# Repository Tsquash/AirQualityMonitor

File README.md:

# Air Quality Monitor

AQM is an ESP32-C6-based, Matter compatible, indoor air-quality monitor. It measures carbon
dioxide, temperature, humidity, VOC, and NOx, displays the latest readings on an e-paper
display, and publishes its measurements through Matter over Wi-Fi. It can also pair with
the companion PM sensor [particle](https://github.com/Tsquash/particle/) over Bluetooth
Low Energy (BLE) to add PM2.5 and PM10 measurements to its existing Matter endpoint.

## Hardware

- **MCU:** Seeed Studio XIAO ESP32-C6
- **Carbon-dioxide sensor:** Sensirion SCD41
- **Temperature and humidity sensor:** ASAIR DHT20
  - Before assembly, pry open the DHT20 module's plastic case and desolder its
    two 10 kΩ I2C pull-up resistors. The AQM PCB already supplies the I2C
    pull-ups, so leaving the module's resistors may cause unexpected errors
- **VOC and NOx sensor:** Sensirion SGP41
  - uses the Sensirion Gas Index Algorithm
- **RTC:** Analog Devices MAX31328
- **Display:** 3.7-inch, 416 x 240 pixel monochrome e-paper display
  - GDEY037T03 panel/UC8253 driver, driven with GxEPD2 and Adafruit GFX libaries
- **PM interconnect:** BLE link to the companion Matter PM sensor
- **Enclosure:** acrylic sandwich-style enclosure

The primary pin assignments are defined in
[`main/sense.cpp`](main/sense.cpp), [`main/screen.cpp`](main/screen.cpp), and
[`main/buttons.h`](main/buttons.h):

| Signal | GPIO |
| --- | ---: |
| I2C SDA | 22 |
| I2C SCL | 23 |
| RTC interrupt | 2 |
| E-paper MOSI | 18 |
| E-paper SCK | 19 |
| E-paper chip select | 17 |
| E-paper data/command | 21 |
| E-paper reset | 20 |
| Top button | 0 |
| Bottom button | 1 |

## Operating modes

### Matter commissioning

The AQM is a Matter-over-Wi-Fi device and requires a 2.4 GHz Wi-Fi network and a
Matter controller. On an uncommissioned device, the display shows the Matter
QR code and manual pairing code. Scan the QR code with a Matter-compatible
controller app and complete the app's setup flow for Matter devices. This project
uses Matter development credentials and is not Matter-certified, so the controller
may ask for confirmation before adding it. Although all devices have the same pairing
code, multiple AQM devices on one network is tested working.

After commissioning, the AQM obtains local time over the network. It determines
the UTC offset from `https://ipapi.co/utc_offset/`, synchronizes system time with
`pool.ntp.org`, writes that time to the MAX31328 RTC, and attempts another RTC
sync once per hour. The hourly sync re-queries the current UTC offset, and supports DST.
If the RTC already contains valid time, the local display can continue operating
before Matter commissioning completes.

### Normal operation

The SGP41 is sampled once per second to maintain the VOC and NOx gas-index
algorithms. Ten seconds before each minute, the RTC wakes the firmware to take
new DHT20 and SCD41 readings, finalize any PM reading received for that minute,
update the Matter attributes, and append CO2, VOC, and NOx values to the
60-sample history. At the start of the next minute, the active display page is
redrawn.

The main page shows the date, time, temperature, relative humidity, CO2, VOC,
NOx, and the overall air-quality level. The second page graphs the most recent
60 one-minute CO2, VOC, and NOx readings. The display performs a full refresh at
`:00` and `:30` each hour and uses partial refreshes between them.

### Linked to a PM sensor

The AQM can pair with the companion Matter PM sensor over BLE.

#### Pairing protocol

Put both devices into pairing mode and keep them nearby:

1. Hold the AQM's bottom button while booting it. Release the button when the
   AQM displays `Pairing with PM`.
2. Start or restart the PM sensor in pairing mode. A new PM sensor automatically
   enters pairing mode on its first boot. On later boots, hold its pair
   button or factory reset button  to force another pairing attempt.
3. Leave both devices powered and nearby until each displays `Pairing
   Successful`. Both pairing windows last up to 120 seconds.

The devices discover and authenticate each other automatically. If either device displays `Pairing
Timed Out`, put both devices back into pairing mode and retry with them nearby.
On success, the PM peer is saved in non-volatile storage and the AQM reconnects
to it automatically on later boots.

The AQM sends its RTC time and measurement schedule to the PM sensor. The PM
sensor returns one-minute PM1.0, PM2.5, and PM10 averages, which the AQM exposes
through Matter. If the BLE connection is interrupted, the AQM retains the last
PM reading for up to three missed minutes and clears it after the fourth. All
other AQM sensing and display functions continue without a linked PM sensor.

## Buttons

| Button | GPIO | At boot | During operation |
| --- | ---: | --- | --- |
| Top | 0 | Erase the complete NVS partition, including Matter commissioning, Wi-Fi credentials, and the saved PM peer | No action |
| Bottom | 1 | Enter PM-pairing mode and replace the previously saved PM peer after successful pairing | Change display page |

A boot action requires the button to be held continuously for at least one second
during the two-second startup check. Factory reset takes priority if both buttons are held.
After a factory reset, the device restarts and displays its Matter commissioning screen.

## Readings

The AQM measures or receives the following values:

- ☁️ **CO2:** measured by the SCD41 and reported in ppm
  - +/- (50 ppm + 2.5% of the reading) from 400 to 1,000 ppm
  - +/- (50 ppm + 3% of the reading) from 1,001 to 2,000 ppm
  - +/- (40 ppm + 5% of the reading) from 2,001 to 5,000 ppm
- 🌡️ **Temperature and 💧relative humidity:** measured by the DHT20
  - Temperature accuracy: +/- 0.75 degrees C
  - Relative-humidity accuracy: +/- 4% RH
- 🍃 **VOC and 💨 NOx indices:** measured by the SGP41 and calculated with the
  [Sensirion Gas Index Algorithm](https://sensirion.com/products/downloads?category=Gas+analyzers)
  as unitless index points from 1 to 500; they are relative air-quality signals,
  not measured gas concentrations
  - VOC's long-term average is 100, lower values indicate improving conditions
    and higher values indicate worsening conditions
  - NOx's typical baseline is 1, values above 1 indicate NOx events
  - Allow approximately one hour for reliable VOC detection and six hours for
    reliable NOx event detection after startup
  - Matter has concentration-measurement clusters for these readings but no
    unit for index points. For compatibility, the firmware
    currently publishes each index through its corresponding concentration
    cluster with the unit set to `µg/m³`. That displayed unit is incorrect:
    the numeric values are still unitless VOC and NOx indices and must not be
    interpreted as physical concentrations.
- **PM1.0, PM2.5, and PM10:** received in micrograms per cubic meter from a
  linked Matter PM sensor

The overall air-quality value is the worst of the current CO2, VOC, NOx, PM1.0,
PM2.5, and PM10 bands. It is reported as Good, Fair, Moderate, Poor, Very Poor,
or Extremely Poor.

## Build, upload, and serial output

Install [PlatformIO](https://platformio.org/) and the Espressif platform
dependencies, connect the XIAO ESP32-C6, then run these commands from the
project directory:

```sh
pio run -e esp32c6
pio run -e esp32c6 -t upload
pio device monitor -b 115200
```

The PlatformIO environment is defined in [`platformio.ini`](platformio.ini).
The project uses the Arduino and ESP-IDF frameworks and is configured for the
`seeed_xiao_esp32c6` board. Serial diagnostics run at 115200 baud. Upload-port
selection may need to be configured for the host computer. A clean or first
compile can take 10 minutes or longer while PlatformIO builds the ESP-IDF and
Matter dependencies, but later incremental builds are faster since the build is cached.

### Bundled MAX31328 library

[`lib/Max31328RTC`](lib/Max31328RTC) is a local fork of Analog Devices'
[MAX31328 Arduino Driver](https://github.com/analogdevicesinc/MAX31328-Arduino-Driver).
The upstream library did not work unchanged with the ESP32-C6, so this fork:

- leaves I2C initialization to the firmware instead of calling `Wire.begin()`
  from the RTC constructor, which would initialize the bus before the AQM
  assigns its SDA and SCL pins;
- casts the write buffer to the byte-pointer type required by the ESP32-C6
  Arduino `Wire.write()` overload, fixing the compile error; and
- updates the time, calendar, and control/status output structures only after a
  successful I2C read, preventing failed reads from copying invalid data.

The upstream driver is licensed under Apache-2.0, which permits modification
and redistribution. The fork retains the upstream copyright and modification
notices and includes the complete license at
[`lib/Max31328RTC/LICENSE.txt`](lib/Max31328RTC/LICENSE.txt).

## License

The original firmware, PCB and schematic files, manufacturing files, enclosure
files, UI assets, and documentation in this repository are available under the
[Apache License 2.0](LICENSE). You may use,
modify, manufacture from, and share, the original or modified project, provided that you follow the license terms :)

## Project layout

```text
main/                  Firmware source, embedded display assets, and component config
  myBitmap/            Embedded monochrome display bitmaps
  myFont/              Embedded Adafruit GFX fonts
lib/                   Project-local libraries, including the altered MAX31328 driver
KICAD/                 PCB schematic, layout, symbols, and footprints
Production/            Manufacturing BOMs and Gerber archive
2D/                    Enclosure and PCB cutout drawings
3D/                    Board, spacer, and enclosure models
UI/                    Display mockups, fonts, and bitmaps
.vscode/               VS Code project configuration
platformio.ini         PlatformIO build environment
LICENSE                Apache License 2.0 project license
sdkconfig.defaults.*   ESP-IDF default configurations
huge_app.csv           ESP-IDF flash partition table
```

The primary firmware files are:

- [`main/main.cpp`](main/main.cpp): boot flow, Matter startup, scheduling, and
  the main loop
- [`main/sense.cpp`](main/sense.cpp): sensor initialization and sampling, gas
  indices, RTC alarms, network time, and overall air-quality calculation
- [`main/screen.cpp`](main/screen.cpp): e-paper initialization, status screens,
  measurement pages, and history graphs
- [`main/buttons.cpp`](main/buttons.cpp): boot-hold detection and display-page
  button handling
- [`main/matter_air_quality_sensor.cpp`](main/matter_air_quality_sensor.cpp):
  Matter endpoint, measurement clusters, and attribute updates
- [`main/pm_link.cpp`](main/pm_link.cpp): BLE PM pairing, reconnection, timing,
  and PM-reading reception
- [`main/pm_protocol.h`](main/pm_protocol.h): BLE data structures shared with
  the companion PM project

## Troubleshooting

- **Matter commissioning does not complete:** Confirm that the Matter controller
  and 2.4 GHz Wi-Fi network are online and that the phone is close enough for
  BLE commissioning. Factory-reset the AQM before retrying it on a different
  Matter fabric or Wi-Fi network.
- **Time or date is incorrect:** The AQM needs network access to the timezone
  API and NTP server. Check the Wi-Fi network's Internet connectivity and
  inspect the serial log for `[Time]` or `[RTC]` errors.
- **A sensor reports invalid or fixed readings:** Check the shared I2C wiring,
  sensor power, and serial output. The firmware logs DHT20, SCD41, SGP41, and RTC
  communication errors.
- **VOC or NOx readings seem unstable after startup:** Leave the device powered
  while the gas-index algorithms learn their baseline. VOC needs about one hour
  and NOx about six hours for reliable event detection.
- **For most other errors:** Check the serial log! I tried to leave debugging print statements that were helpful to me during development.

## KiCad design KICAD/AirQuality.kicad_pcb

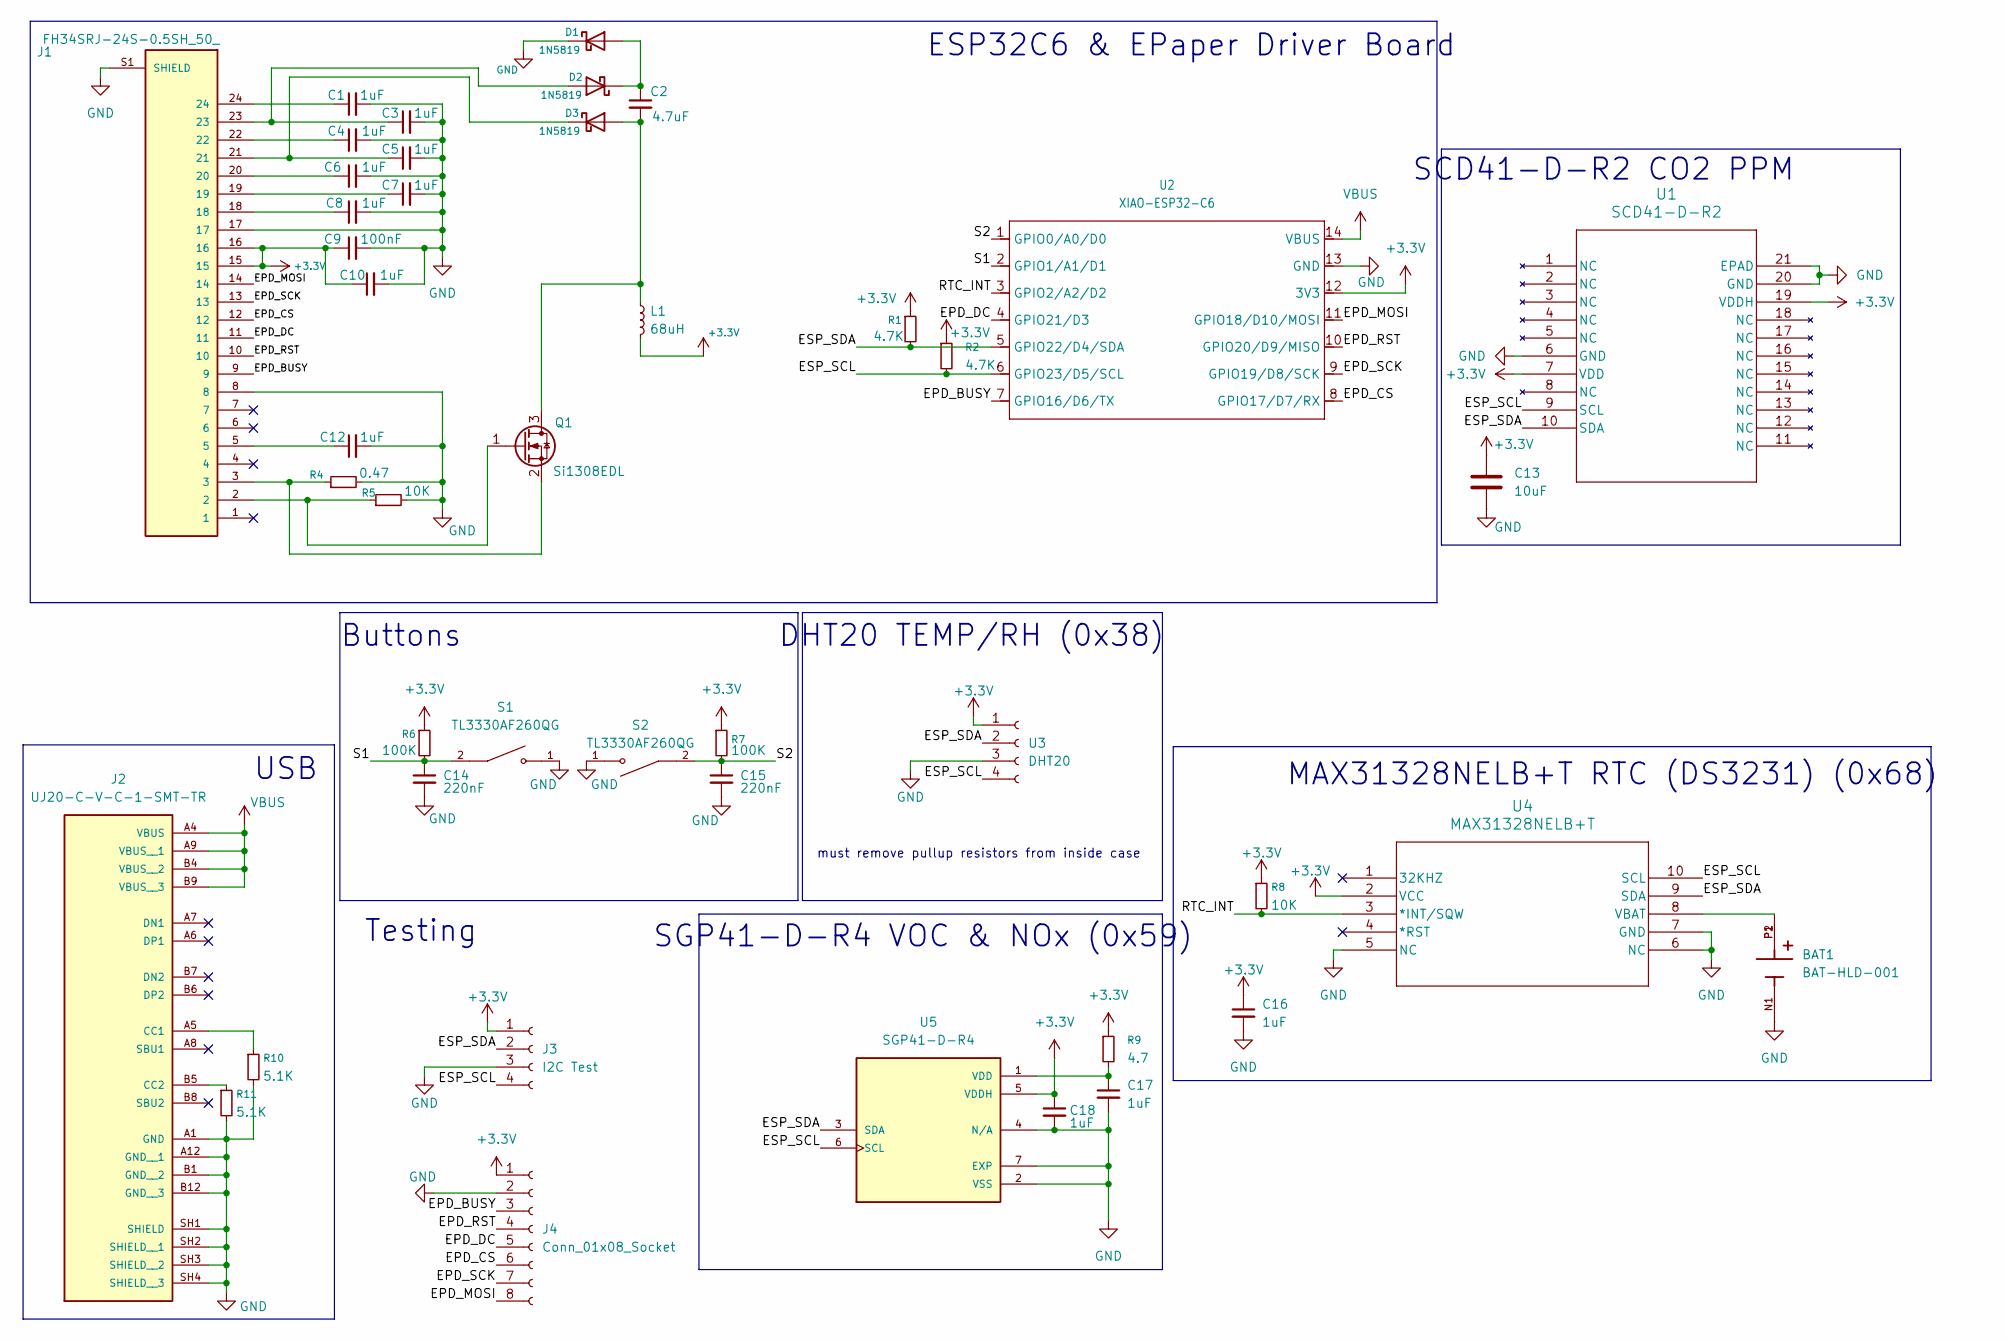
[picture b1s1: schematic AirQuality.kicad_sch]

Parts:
BAT1: BAT-HLD-001; BAT_BAT-HLD-001; PARTREV C
C1, C3, C4, C5, C6, C7, C8, C10, C12, C16, C17, C18: 1uF; C_0603_1608Metric
C2: 4.7uF; C_0603_1608Metric
C9: 100nF; C_0603_1608Metric
C13: 10uF; C_0603_1608Metric
C14, C15: 220nF; C_0603_1608Metric
D1, D2, D3: 1N5819; D_SOD-123
J1: FH34SRJ-24S-0.5SH_50_; HRS_FH34SRJ-24S-0.5SH_50_
J2: UJ20-C-V-C-1-SMT-TR; CUI_UJ20-C-V-C-1-SMT-TR; PARTREV 1.0
J3: I2C Test; PinHeader_1x04_P2.54mm_Vertical
J4: Conn_01x08_Socket; PinHeader_1x08_P2.54mm_Vertical
L1: 68uH; L_0805_2012Metric
Q1: Si1308EDL; SOT-323_SC-70
R1, R2: 4.7K; R_0603_1608Metric
R4: 0.47; R_0603_1608Metric
R5, R8: 10K; R_0603_1608Metric
R6, R7: 100K; R_0603_1608Metric
R9: 4.7; R_0603_1608Metric
R10, R11: 5.1K; R_0603_1608Metric
S1, S2: TL3330AF260QG; SW_TL3330AF260QG; PARTREV B
U1: SCD41-D-R2; QFN20_SCD41-D-R2_SEN
U2: XIAO-ESP32-C6; XIAO-ESP32C6-DIP
U3: DHT20; PinHeader_1x04_P2.54mm_Vertical
U4: MAX31328NELB+T; 21-0140AK_L1055M-1_MXM
U5: SGP41-D-R4; XDCR_SGP41-D-R4; PARTREV 1.0

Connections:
+3.3V: C9.1, C10.1, C13.1, C16.1, C18.1, J1.15, J1.16, J3.1, J4.1, L1.2, R1.1, R2.1, R6.1, R7.1, R8.1, R9.1, U1.7 (VDD), U1.19 (VDDH), U2.12 (3V3), U3.1, U4.2 (VCC), U5.5 (VDDH); also elsewhere on the board
/EPD_BUSY: J1.9, J4.3, U2.7 (GPIO16/D6/TX)
/EPD_CS: J1.12, J4.6, U2.8 (GPIO17/D7/RX)
/EPD_DC: J1.11, J4.5, U2.4 (GPIO21/D3)
/EPD_MOSI: J1.14, J4.8, U2.11 (GPIO18/D10/MOSI)
/EPD_RST: J1.10, J4.4, U2.10 (GPIO20/D9/MISO)
/EPD_SCK: J1.13, J4.7, U2.9 (GPIO19/D8/SCK)
/ESP_SCL: J3.4, R2.2, U1.9 (SCL), U2.6 (GPIO23/D5/SCL), U3.4, U4.10 (SCL), U5.6 (SCL)
/ESP_SDA: J3.2, R1.2, U1.10 (SDA), U2.5 (GPIO22/D4/SDA), U3.2, U4.9 (SDA), U5.3 (SDA)
/RTC_INT: R8.2, U2.3 (GPIO2/A2/D2), U4.3 (*INT/SQW)
/S1: C14.1, R6.2, S1.2, U2.2 (GPIO1/A1/D1)
/S2: C15.1, R7.2, S2.2, U2.1 (GPIO0/A0/D0)
GND: BAT1.N1, C1.2, C3.2, C4.2, C5.2, C6.2, C7.2, C8.2, C9.2, C10.2, C12.2, C13.2, C14.2, C15.2, C16.2, C17.2, C18.2, D1.1 (K), J1.8, J1.17, J1.S1 (SHIELD), J1.S2 (SHIELD), J2.A1 (GND), J2.A12 (GND__1), J2.B1 (GND__2), J2.B12 (GND__3), J2.SH1 (SHIELD), J2.SH2 (SHIELD__1), J2.SH3 (SHIELD__2), J2.SH4 (SHIELD__3), J3.3, J4.2, R4.2, R5.2, R10.2, R11.2, S1.1, S2.1, U1.6 (GND), U1.20 (GND), U1.21 (EPAD), U2.13 (GND), U3.3, U4.5 (NC), U4.6 (NC), U4.7 (GND), U5.2 (VSS), U5.4 (N/A), U5.7 (EXP); also elsewhere on the board
unnamed: C1.1, J1.24
unnamed: C4.1, J1.22
unnamed: C6.1, J1.20
unnamed: C7.1, J1.19
unnamed: C8.1, J1.18
unnamed: C12.1, J1.5
unnamed: C2.1, D1.2 (A), D2.1 (K)
unnamed: C3.1, D2.2 (A), J1.23
unnamed: C2.2, D3.2 (A), L1.1, Q1.3 (D)
unnamed: C5.1, D3.1 (K), J1.21
unnamed 23: J1.4; also elsewhere on the board
unnamed: J2.A5 (CC1), R10.1
unnamed: J2.B5 (CC2), R11.1
unnamed: J1.2, Q1.1 (G), R5.1
unnamed: J1.3, Q1.2 (S), R4.1
unnamed: BAT1.P1, BAT1.P2, U4.8 (VBAT)
unnamed: C17.1, R9.2, U5.1 (VDD)
VBUS: J2.A4 (VBUS), J2.A9 (VBUS__1), J2.B4 (VBUS__2), J2.B9 (VBUS__3), U2.14 (VBUS)

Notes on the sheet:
SGP41-D-R4 VOC & NOx (0x59)
ESP32C6 & EPaper Driver Board
DHT20 TEMP/RH (0x38)
USB
Buttons
Testing
MAX31328NELB+T RTC (DS3231) (0x68)
SCD41-D-R2 CO2 PPM
must remove pullup resistors from inside case

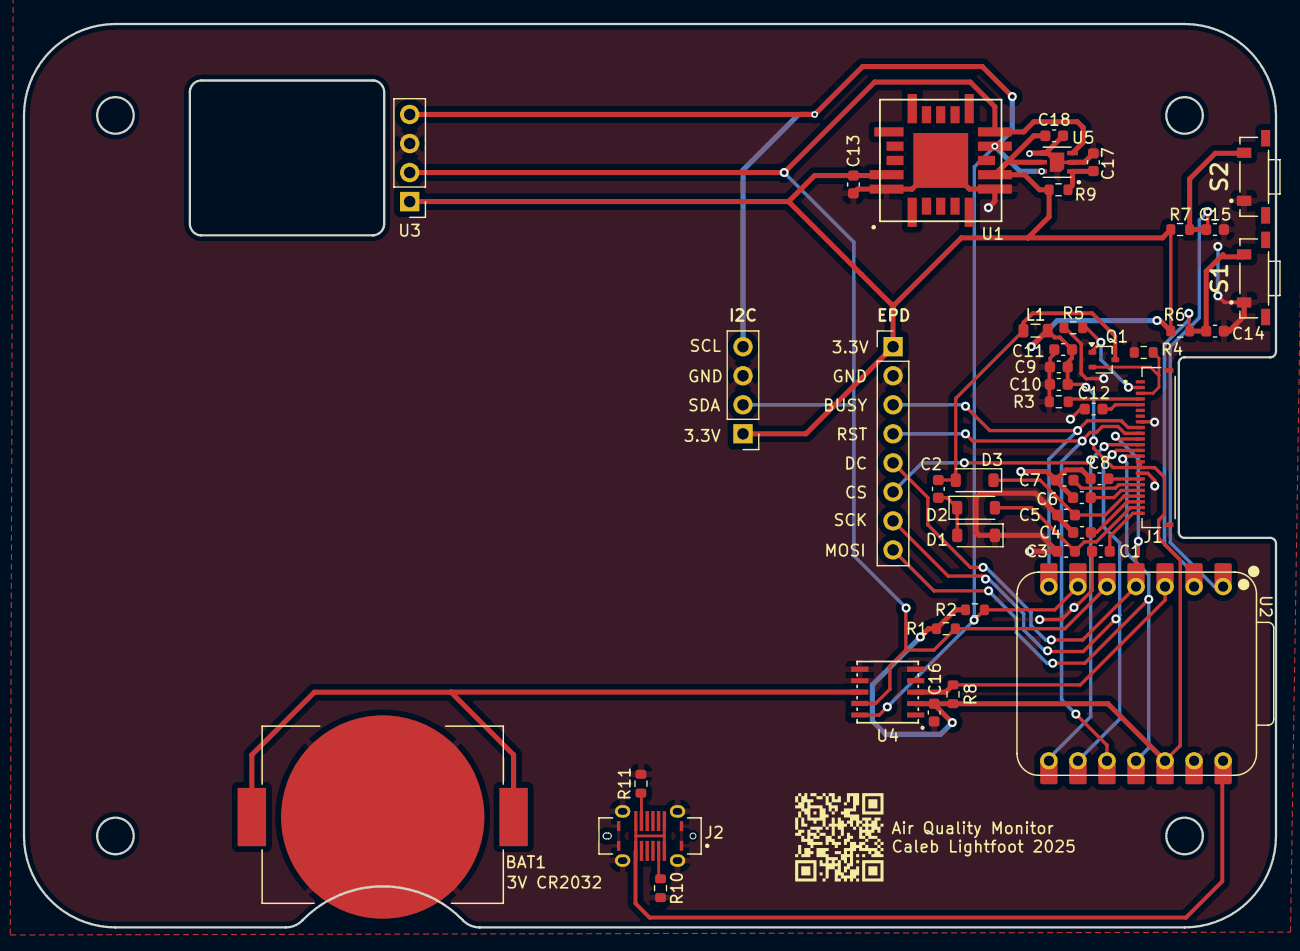
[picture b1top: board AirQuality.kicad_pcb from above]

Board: 4 copper layers, 109.5 x 79.0 mm, 46 parts (0 on the bottom side), 31 nets.

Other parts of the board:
C11: 4.7uF; C_0603_1608Metric
R3: 0; R_0603_1608Metric

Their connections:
+3.3V: C11.1; also elsewhere on the board
GND: C11.2, R3.2; also elsewhere on the board
unnamed 23: R3.1; also elsewhere on the board

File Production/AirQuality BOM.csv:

Reference,Qty,Value,Footprint,,
BAT1,1,BAT-HLD-001,AirQualityFootprints:BAT_BAT-HLD-001,,
"C1,C3,C4,C5,C6,C7,C8,C10,C12,C16,C17,C18",12,1uF,Capacitor_SMD:C_0603_1608Metric,,
"C2,C11",2,4.7uF,Capacitor_SMD:C_0603_1608Metric,,
C9,1,100nF,Capacitor_SMD:C_0603_1608Metric,,
C13,1,10uF,Capacitor_SMD:C_0603_1608Metric,,
"C14,C15",2,220nF,Capacitor_SMD:C_0603_1608Metric,,*need to desolder two
"D1,D2,D3",3,1N5819,Diode_SMD:D_SOD-123,,
J1,1,FH34SRJ-24S-0.5SH_50_,AirQualityFootprints:HRS_FH34SRJ-24S-0.5SH_50_,,
J2,1,UJ20-C-V-C-1-SMT-TR,AirQualityFootprints:CUI_UJ20-C-V-C-1-SMT-TR,,
L1,1,68uH,Inductor_SMD:L_0805_2012Metric,,
Q1,1,Si1308EDL,Package_TO_SOT_SMD:SOT-323_SC-70,,
"R1,R2",2,4.7K,Resistor_SMD:R_0603_1608Metric,,
R3,1,DNP,Resistor_SMD:R_0603_1608Metric,,
R4,1,0.47,Resistor_SMD:R_0603_1608Metric,,
R5,1,10K/0,Resistor_SMD:R_0603_1608Metric,,
"R6,R7",2,100K,Resistor_SMD:R_0603_1608Metric,,
R8,1,10K,Resistor_SMD:R_0603_1608Metric,,
R9,1,4.7,Resistor_SMD:R_0603_1608Metric,,
"R10,R11",2,5.1K,Resistor_SMD:R_0603_1608Metric,,
"S1,S2",2,TL3330AF260QG,AirQualityFootprints:SW_TL3330AF260QG,,
U1,1,SCD41-D-R2,AirQualityFootprints:QFN20_SCD41-D-R2_SEN,,
U2,1,XIAO-ESP32-C6,AirQualityFootprints:XIAO-ESP32C6-DIP,,*need to desolder one
U3,1,DHT20,Connector_PinHeader_2.54mm:PinHeader_1x04_P2.54mm_Vertical,,*need to desolder one
U4,1,MAX31328NELB+T,AirQualityFootprints:21-0140AK_L1055M-1_MXM,,*need to desolder one
U5,1,SGP41-D-R4,AirQualityFootprints:XDCR_SGP41-D-R4,,

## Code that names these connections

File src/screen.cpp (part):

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
#define GxEPD2_DISPLAY_CLASS GxEPD2_BW
#define GxEPD2_DRIVER_CLASS GxEPD2_370_GDEY037T03 // GDEY037T03 240x416, UC8253
#define EPD_DC 21
#define EPD_CS 17
#define EPD_SCK   19
#define EPD_MOSI  18
#define EPD_MISO -1 // not reading from screen
#define EPD_BUSY -1 // can set to -1 to not use a pin (will wait a fixed delay)
#define SRAM_CS -1 // use internal RAM
#define EPD_RESET 20  // can set to -1 and share with microcontroller Reset!
#define EPD_SPI &epd_spi // primary SPI
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
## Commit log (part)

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2025-12-30 initial
2025-12-31 added battery monitoring, shows percent on screen
2025-12-31 working Eink with battery %, temp, and humidity showing (basic)
2025-12-31 added lib dep for interrupt buttons
2025-12-31 removed .vscode folder from project
2025-12-31 removed unused EPD drivers and panels for compile time, added basic (non-working) button functions
2025-12-31 check if buttons held at boot working
2025-12-31 added license, added wifi functionality for setting RTC and captive portal config, changed C6 partition scheme to free up flash, modified boot button logic, and removed EPD examples
2026-01-02 RTC boot logic is working, actually setting RTC from NTP is .... non working? Everything WiFi related working, just fix NTP->RTC
2026-01-03 try to stay on topic on a branch impossible edition. Setting time on the RTC works now, RTC lib moved locally to solve TWO errors with the ESP32C6, and device now knows if its coming off a reboot
2026-01-03 added explicit notes where MAX31328 library was changed to comply with apache license
2026-01-03 removed unused settings and added on topic settings, also changed screen/sense to adapt to config
2026-01-05 this things lowkey got a UI now
2026-01-06 page2 graphs and graphics are working with mock data
2026-01-12 RTC alarms working, B&W screen added
2026-01-22 initial non working esp-idf work
2026-01-22 added fonts and bitmaps
2026-01-25 b&w screens working on new pcbs
2026-01-25 co2 functions, button changes page
2026-01-27 fast refresh, button debouncing, gxepd2, queues populate, graphs have scales
2026-02-03 partial refresh fully working??
2026-02-04 switching to test old partial behavior, state machine still behaving the same
2026-02-04 partial after full to fix bug
2026-02-05 change referesh interval parameter
2026-02-11 working matter without C02 but with temp and humidity
2026-02-11 reporting temperature, humidity, air quality, and CO2 over matter
2026-02-14 all readings working in homekit (VOC & NOX wrong unit)
2026-03-06 new UI
2026-03-06 removed all old config files
2026-03-08 production code. fixed weekday issue
2026-03-10 removed managed components, updated readme
2026-03-16 added binaries for quickly reflashing
